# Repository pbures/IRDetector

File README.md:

# IRDetector

This is a skeleton project containing just a concepts for now.
The project is to provide a detector of an IR controller. The 
code supports now 2 IR sensors simultaneously and the NEC protocol.

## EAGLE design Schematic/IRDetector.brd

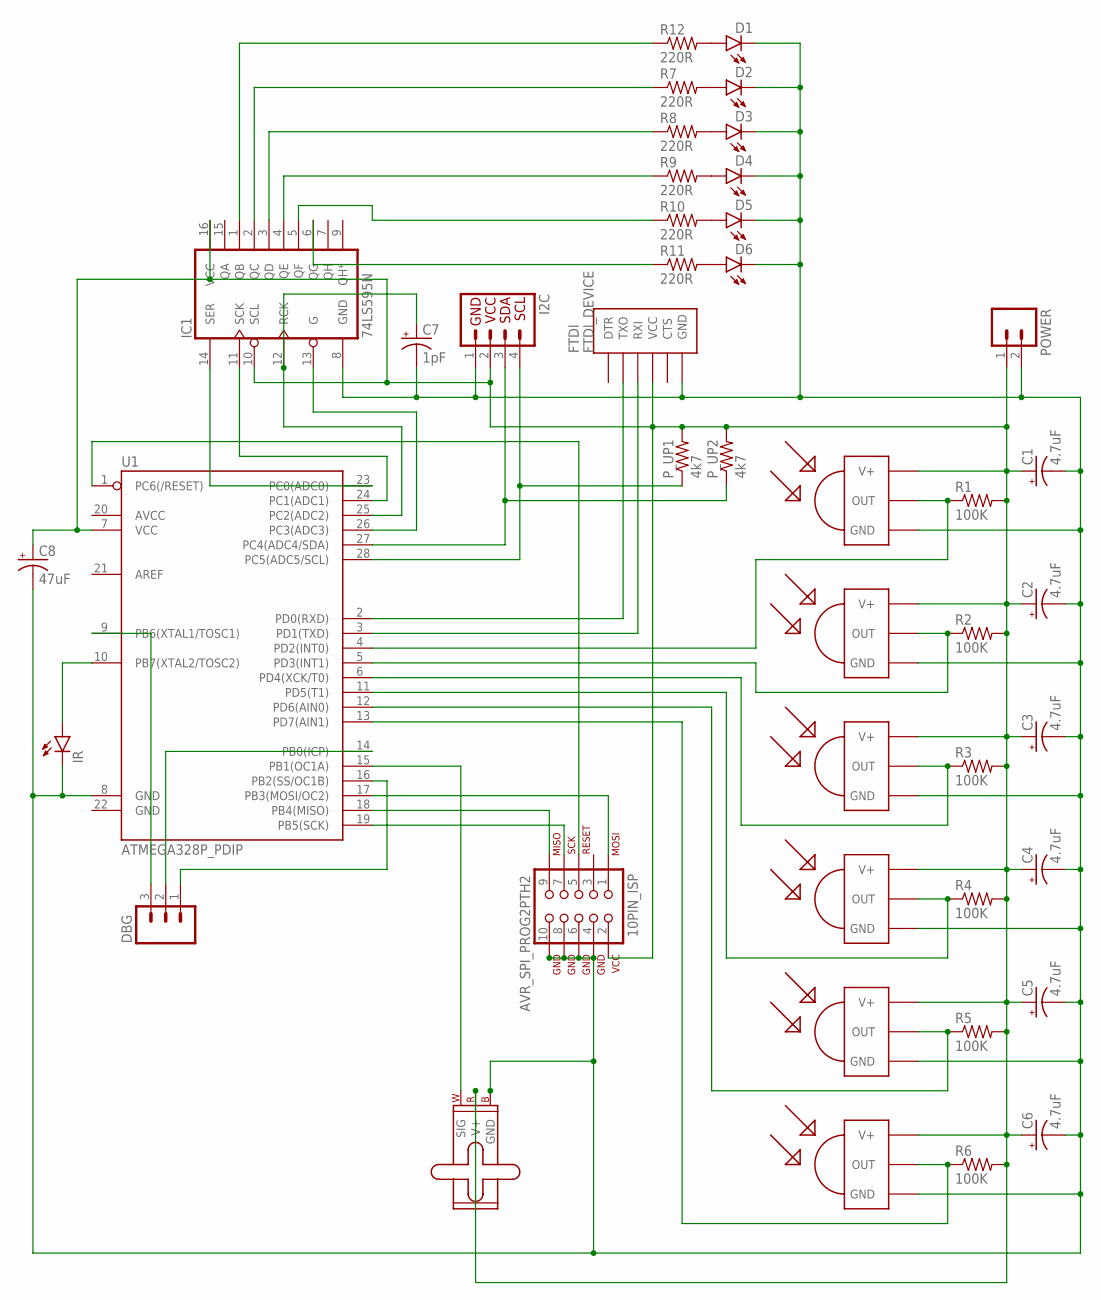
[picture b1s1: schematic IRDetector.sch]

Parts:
10PIN_ISP: AVR_SPI_PROG2PTH2; 2X5-SHROUDED
C1, C2, C3, C4, C5, C6: 4.7uF; CPOL-RADIAL-10UF-25V
C7: 1pF; CPOL-RADIAL-10UF-25V
C8: 47uF; CPOL-RADIAL-10UF-25V
D1, D2, D3, D4, D5, D6: LED5MM
DBG: M03PTH; 1X03
FTDI: FTDI_DEVICE; FTDI_DEVICE_SIDE
I2C: I2C_STANDARD; 1X04
IC1: 74LS595N; DIL16
IR: LED5MM
IRD1, IRD2, IRD3, IRD4, IRD5, IRD6: TSOP4838; TSOP18XX
M1: SMALL_SERVO; 1X03
POWER: M02JST-PTH-VERT; JST-2-PTH-VERT
P_UP1, P_UP2: 4k7; 1/6W-RES
R1, R2, R3, R4, R5, R6: 100K; 1/6W-RES
R7, R8, R9, R10, R11, R12: 220R; 1/6W-RES
U1: ATMEGA328P_PDIP; DIL28-3

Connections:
unnamed: 10PIN_ISP.4 (GND), 10PIN_ISP.6 (GND), 10PIN_ISP.8 (GND), 10PIN_ISP.10 (GND), C1.2 (-), C2.2 (-), C3.2 (-), C4.2 (-), C5.2 (-), C6.2 (-), C7.2 (-), C8.2 (-), D1.K (C), D2.K (C), D3.K (C), D4.K (C), D5.K (C), D6.K (C), FTDI.P$6 (GND), I2C.1, IC1.8 (GND), IR.K (C), IRD1.GND, IRD2.GND, IRD3.GND, IRD4.GND, IRD5.GND, IRD6.GND, M1.3 (GND), POWER.2, U1.8 (GND)
unnamed: 10PIN_ISP.2 (VCC), C1.1 (+), C2.1 (+), C3.1 (+), C4.1 (+), C5.1 (+), C6.1 (+), C8.1 (+), FTDI.P$4 (VCC), I2C.2, IC1.10 (SCL), IC1.16 (VCC), IRD1.VCC (V+), IRD2.VCC (V+), IRD3.VCC (V+), IRD4.VCC (V+), IRD5.VCC (V+), IRD6.VCC (V+), M1.2 (V+), POWER.1, P_UP1.2, P_UP2.2, R1.2, R2.2, R3.2, R4.2, R5.2, R6.2, U1.7 (VCC)
unnamed: IRD1.OUT, R1.1, U1.4 (PD2(INT0))
unnamed: IRD2.OUT, R2.1, U1.5 (PD3(INT1))
unnamed: IRD3.OUT, R3.1, U1.6 (PD4(XCK/T0))
unnamed: IRD4.OUT, R4.1, U1.11 (PD5(T1))
unnamed: IRD5.OUT, R5.1, U1.12 (PD6(AIN0))
unnamed: IRD6.OUT, R6.1, U1.13 (PD7(AIN1))
unnamed: FTDI.P$2 (TXO), U1.2 (PD0(RXD))
unnamed: FTDI.P$3 (RXI), U1.3 (PD1(TXD))
unnamed: 10PIN_ISP.5 (RESET), U1.1 (PC6(/RESET))
unnamed: 10PIN_ISP.9 (MISO), U1.18 (PB4(MISO))
unnamed: 10PIN_ISP.1 (MOSI), U1.17 (PB3(MOSI/OC2))
unnamed: M1.1 (SIG), U1.15 (PB1(OC1A))
unnamed: 10PIN_ISP.7 (SCK), U1.19 (PB5(SCK))
unnamed: IC1.13 (G), U1.26 (PC3(ADC3))
unnamed: C7.1 (+), IC1.12 (RCK), U1.25 (PC2(ADC2))
unnamed: IC1.11 (SCK), U1.24 (PC1(ADC1))
unnamed: IC1.1 (QB), R12.1
unnamed: IC1.14 (SER), U1.23 (PC0(ADC0))
unnamed: I2C.4, P_UP1.1, U1.28 (PC5(ADC5/SCL))
unnamed: I2C.3, P_UP2.1, U1.27 (PC4(ADC4/SDA))
unnamed: IC1.2 (QC), R7.1
unnamed: IC1.3 (QD), R8.1
unnamed: IC1.4 (QE), R9.1
unnamed: D1.A, R12.2
unnamed: D2.A, R7.2
unnamed: D3.A, R8.2
unnamed: D4.A, R9.2
unnamed: D5.A, R10.2
unnamed: D6.A, R11.2
unnamed: IR.A, U1.10 (PB7(XTAL2/TOSC2))
unnamed: DBG.1, U1.16 (PB2(SS/OC1B))
unnamed: DBG.2, U1.14 (PB0(ICP))
unnamed: IC1.5 (QF), R10.1
unnamed: IC1.6 (QG), R11.1
unnamed: DBG.3, U1.9 (PB6(XTAL1/TOSC1))

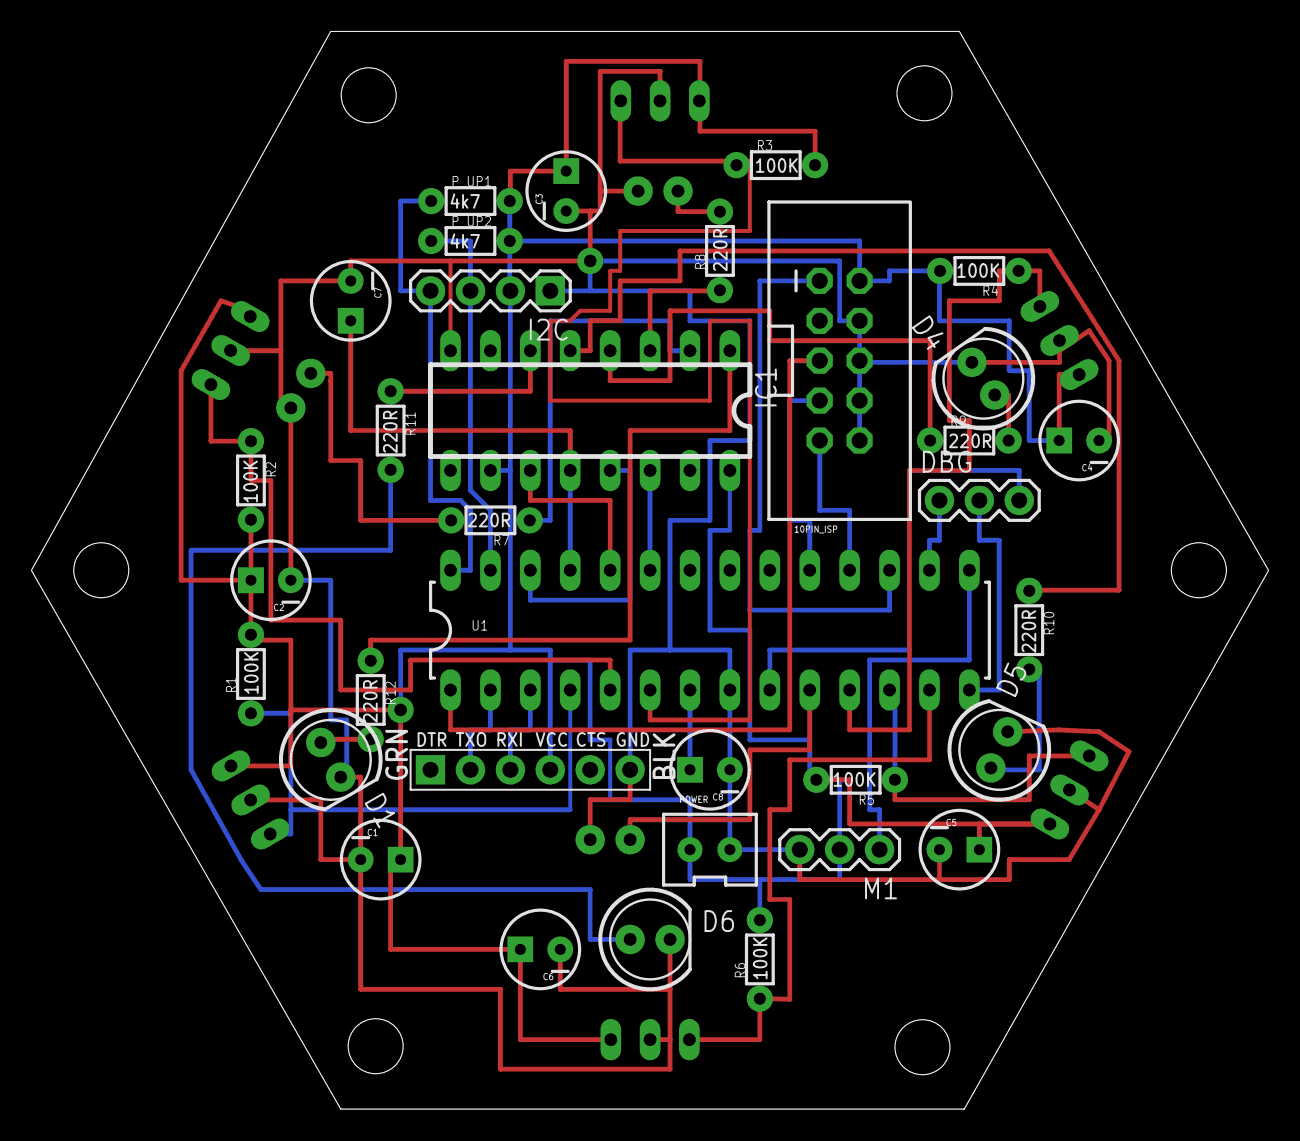
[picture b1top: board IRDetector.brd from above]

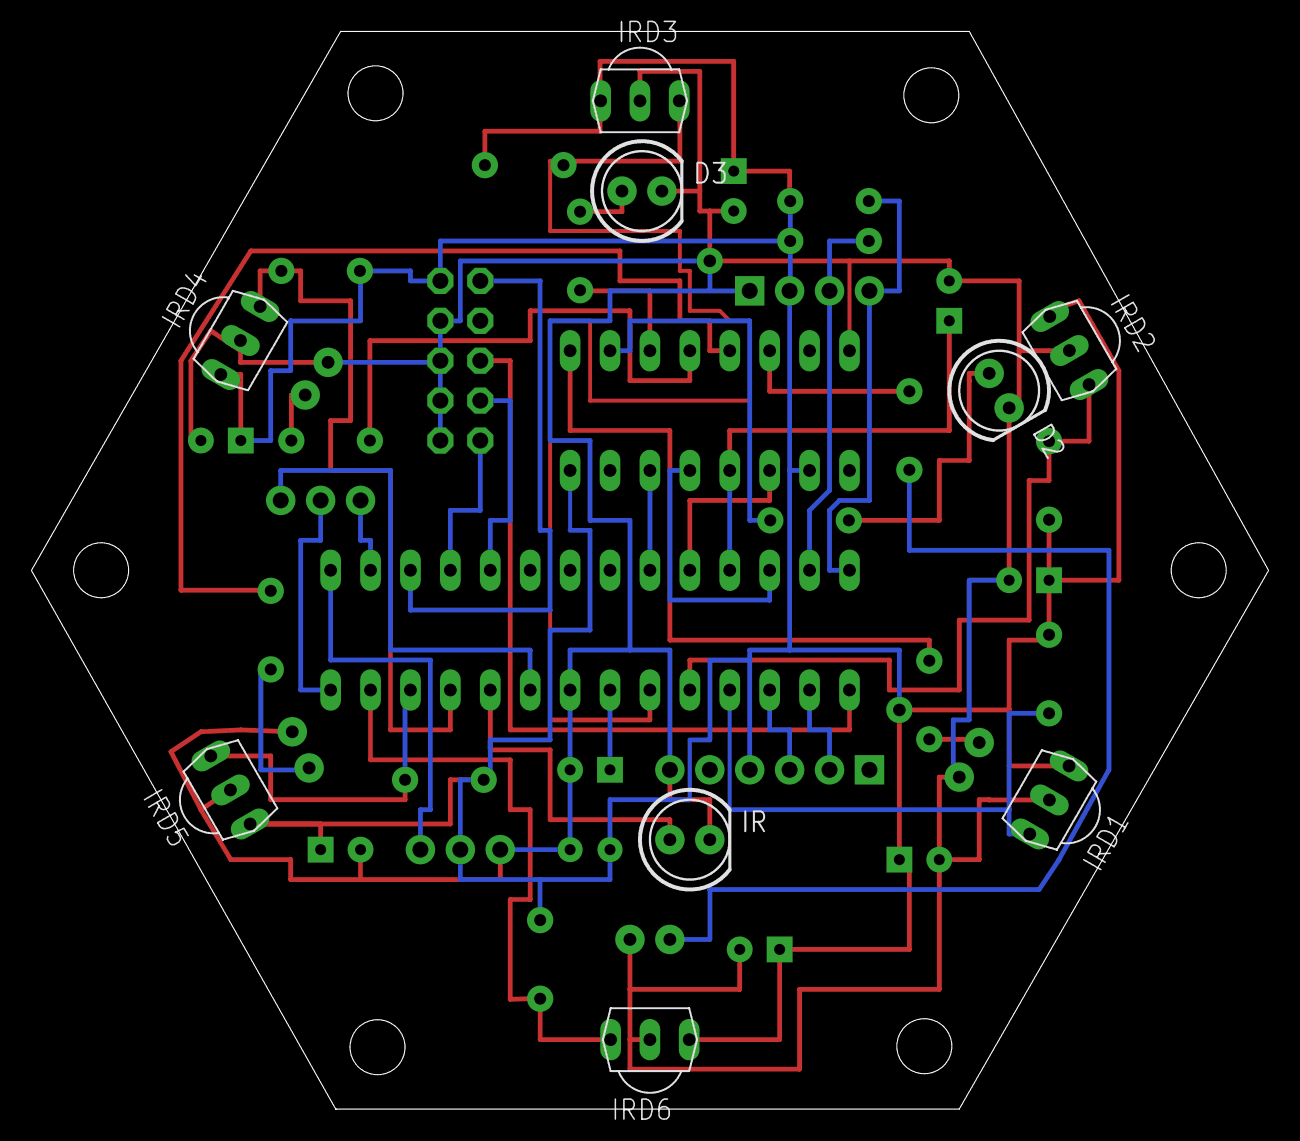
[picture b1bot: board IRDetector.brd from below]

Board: 2 copper layers, 78.7 x 68.6 mm, 43 parts (9 on the bottom side), 37 nets.

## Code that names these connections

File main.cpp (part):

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#endif

/*
 * Initialize receivers on pins D, PD2, PD3, ....
 */
void initReceivers() {

	DDRD &= ~((1 << PD2) | (1 << PD3) | (1 << PD4) | (1 << PD5) | (1 << PD6)
			| (1 << PD7));
	PORTD |= ((1 << PD2) | (1 << PD3) | (1 << PD4) | (1 << PD5) | (1 << PD6)
			| (1 << PD7));

	/* Enable the pin change interrupts on these three pins corresponding to PD2, PD3, ... */
	PCICR |= (1 << PCIE2);
	PCMSK2 |= ((1 << PCINT18) | (1 << PCINT19) | (1 << PCINT20) | (1 << PCINT21)
			| (1 << PCINT22) | (1 << PCINT23));
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	TCCR1A |= (1 << COM1A1);

	ICR1 = 20000; //20ms cycle.
	DDRB |= (1 << PB1);

	OCR1A = 1500;
}
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
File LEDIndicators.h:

/*
 * LEDIndicators.h
 *
 *  Created on: 11. 11. 2016
 *      Author: pbures
 */

#ifndef LEDINDICATORS_H_
#define LEDINDICATORS_H_

#define SR_PORT PORTC
#define SR_DDR  DDRC
#define SR_DTA  PC0 /* This is data signal */
#define SR_CLK  PC1 /* When value goes from low to high, the DTA is stored and values shifted */
#define SR_LAT  PC2 /* Keep low while writing to it */
#define SR_OE   PC3  /*Keep low for output enable */

#include <stdint.h>
#include <avr/io.h>
#include "config.h"
#include "pindefs.h"

/*
 * Drives up to 8 LEDs, enabling or disabling them.
 * This is a driver.
 * TODO: Make sure this is verified on a hardware!
 */
class LEDIndicators {
public:
	static void init();
	static void setLeds(uint8_t leds);
};

#endif /* LEDINDICATORS_H_ */

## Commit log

2016-10-18 first commit of a first working draft
2016-10-22 Added third channel.
2016-10-22 Changed the logic to keep servicing the pin chnage ISR
2016-10-22 Modified the PCIFR test and reread of the PINC input.
2016-10-22 Optimized time computation and the ISR in general.
2016-10-22 Started work on decoder called from main, so ISR servicing the PCINT events is not too overloaded. Next step is to decode the gaps[][] channels using the very same state machine.
2016-10-23 Moved the evaluation of edge into separate funtion as a preparation for processing in main.
    Fixed few issues with NUM_CHANNELLS hardcoded to 3.
2016-10-23 Implemted the option to decode in main.
    The problem is now the memory, we are storing 256 edges for each channel
    which is enough for 3 commands. Need to optimize that.
    The ISR processing is down from 160 to 100 us.
2016-10-25 Time gaps computation optimalized, decreased granularity via prescaler.
2016-10-27 Implemented time sweeping histogram.
2016-11-05 Modify to process the edges in the main loop.
2016-11-05 Changed the timer for time measurement to Timer0. The Timer1 was not necessary.
2016-11-05 Created a schematic for the detector.
2016-11-06 Modified to use PD2...PD7 as an input for the IR receivers, so it is aligned with the schematics.
2016-11-06 Minor modification to reflect debug pins in code and schema
2016-11-06 Created Histogram and CmdBuffer classes. Needs testing on real HW.
2016-11-08 Moved to OOP approach the CmdBuffer class. Verified with the setup.
2016-11-08 Finished Histogram implementation. Reworked CmdBuffer so more iterators can work on top of it.
2016-11-11 Moved to OOP using templates. The ring buffer may hold any structure now.
2016-11-11 Board design created.
2016-11-11 Added LED indications code.
2016-11-11 Changed to use stdio printf. Changed the UART ipmlementaton to use the one from Tomas.
2016-11-19 Fixed bug with the shift regirster.
2016-11-23 Changed timer measuring to Timer1. The timer0 will be used for IR for modulation on PD6 pin.
    Moved the IR LED functionality to new class IRTransciever.

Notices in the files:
parts and their libraries:
SparkFun-Connectors: Licensing: Creative Commons ShareAlike 4.0 International - https://creativecommons.org/licenses/by-sa/4.0
